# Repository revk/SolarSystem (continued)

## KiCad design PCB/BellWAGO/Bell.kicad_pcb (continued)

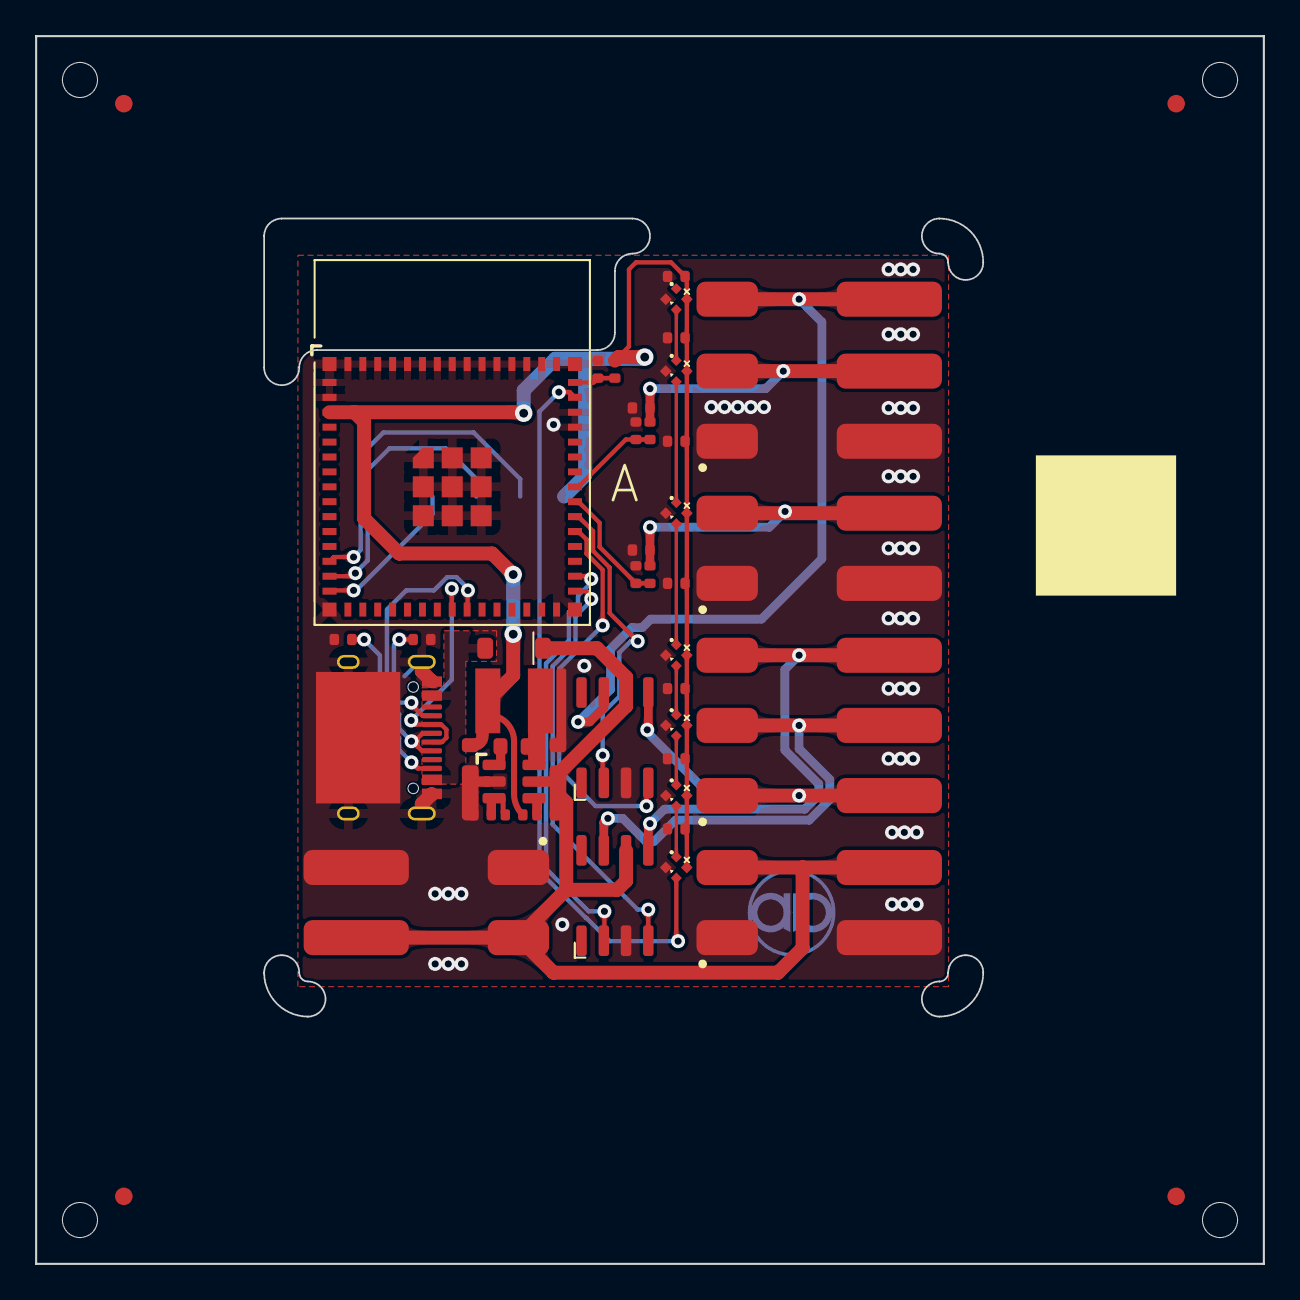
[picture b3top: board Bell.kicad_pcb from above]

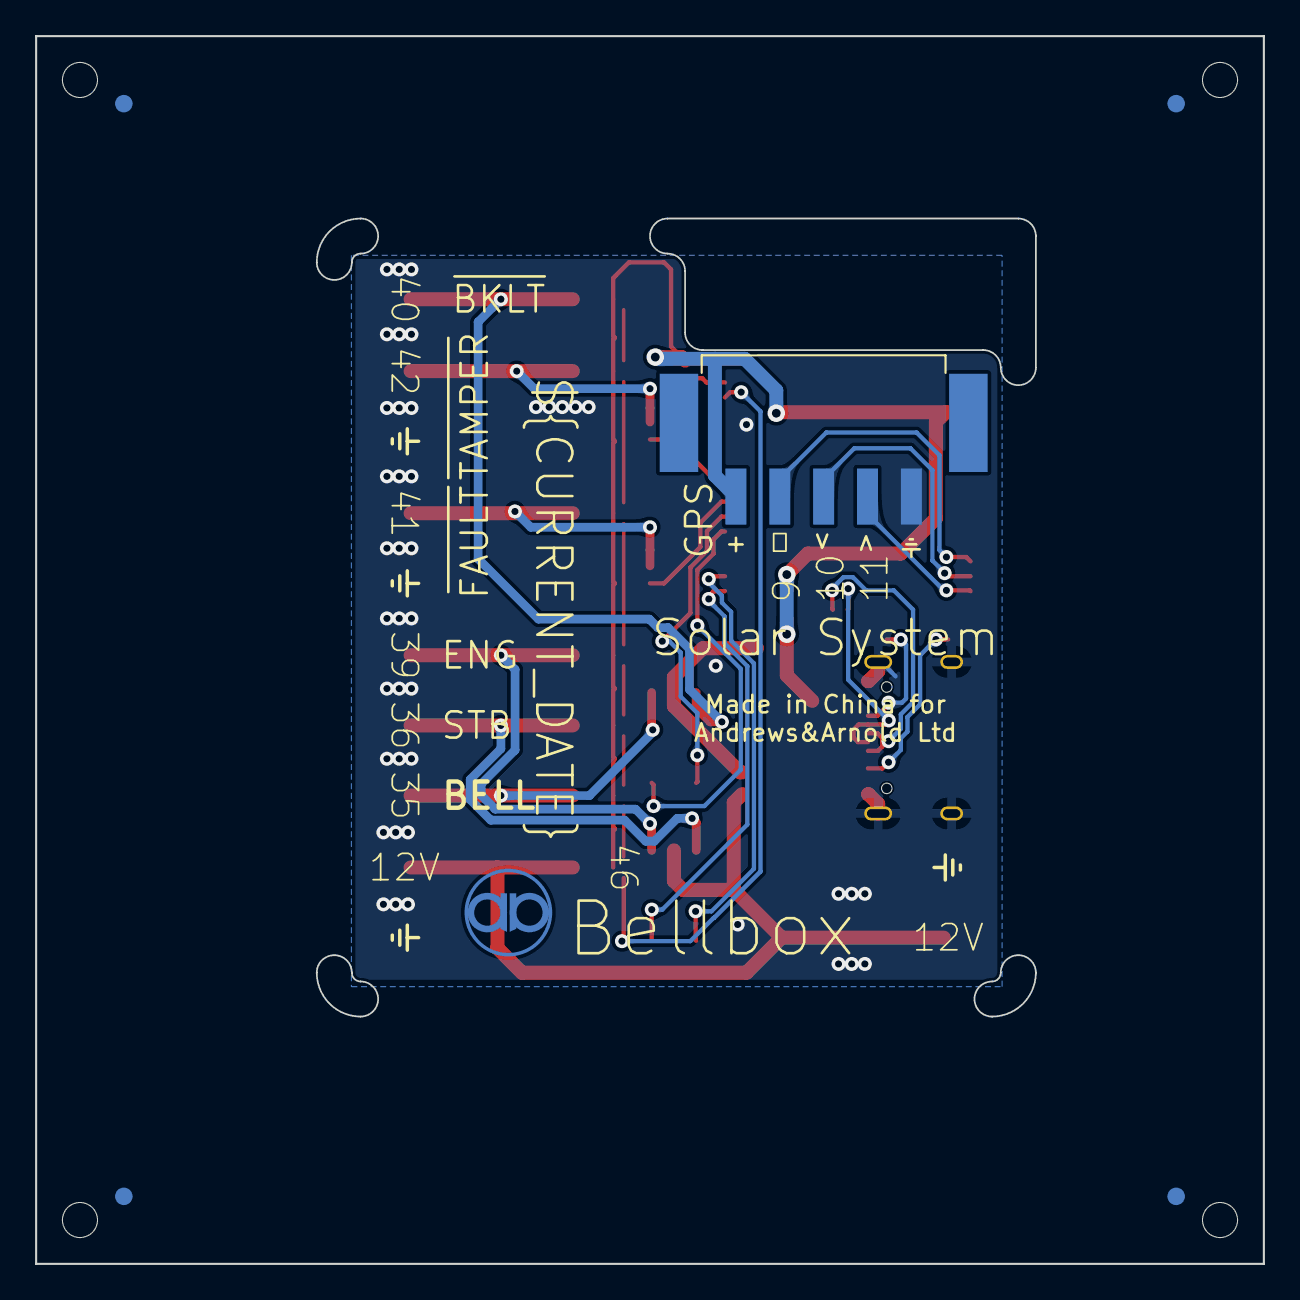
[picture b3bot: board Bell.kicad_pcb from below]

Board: 2 copper layers, 70.0 x 70.0 mm, 50 parts (3 on the bottom side), 31 nets.

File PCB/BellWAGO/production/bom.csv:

Designator,Footprint,Quantity,Value,LCSC Part #
C1,C_0603_,1,10uF 35V,C194427
"C10, C11, C12, C13, C4, C5, C6",C_0402,7,100nF,
"C2, C3",C_0402,2,33pF,
C7,C_0603_,1,10uF 6.3V,C1691
C8,C_0402,1,1uF,
C9,C_0603_,1,100nF,
"D1, D10",DFN1006-2L,2,~,C5137770
"D2, D4, D5, D6, D7, D8, D9",SMD1010,7,XL-1010RGBC-WS2812B,C5349953
D3,D_SOD-123,1,MBR0530,C5204746
J1,USB-C-Socket-H,1,USB-C-Socket-V,C709357
"J10, J11",WAGO-2060-452-998-404,2,FAULT,C2765055
J2,WAGO-2060-451-998-404,1,BL,C2765054
J7,WAGO-2060-453-998-404,1,BELL,C2765056
"J8, J9",WAGO-2060-452-998-404,2,PWR,C2765055
L2,L_4x4_,1,10uH,C167879
R1,R_0402_,1,124k,
R2,R_0402_,1,40k2,
R3,R_0402_,1,1M,
"R4, R7",R_0402,2,100R,
"R5, R6",R_0402,2,5K1,
R8,R_0402,1,10K,
U1,SOT-23-6-MD8942,1,MD8942,C2684786
"U3, U4",SO-8_3.9x4.9mm_P1.27mm,2,ISL89410,C635887
U6,ESP32-S3-MINI-1,1,ESP32-S3-MINI-1,C3013941

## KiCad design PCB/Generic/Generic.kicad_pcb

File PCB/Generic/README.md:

# Generic

These files are for use in [KiCad](https://www.kicad.org).

## Trademark

This is an open source project, but bear in mind you cannot sell boards bearing the Andrews & Arnold Ltd name, the A&A logo, the registered trademark AJK logo, or the GS1 allocated EANs assigned to Andrews & Arnold Ltd.

## Images

*Auto generated 2025-08-12T13:39:20*

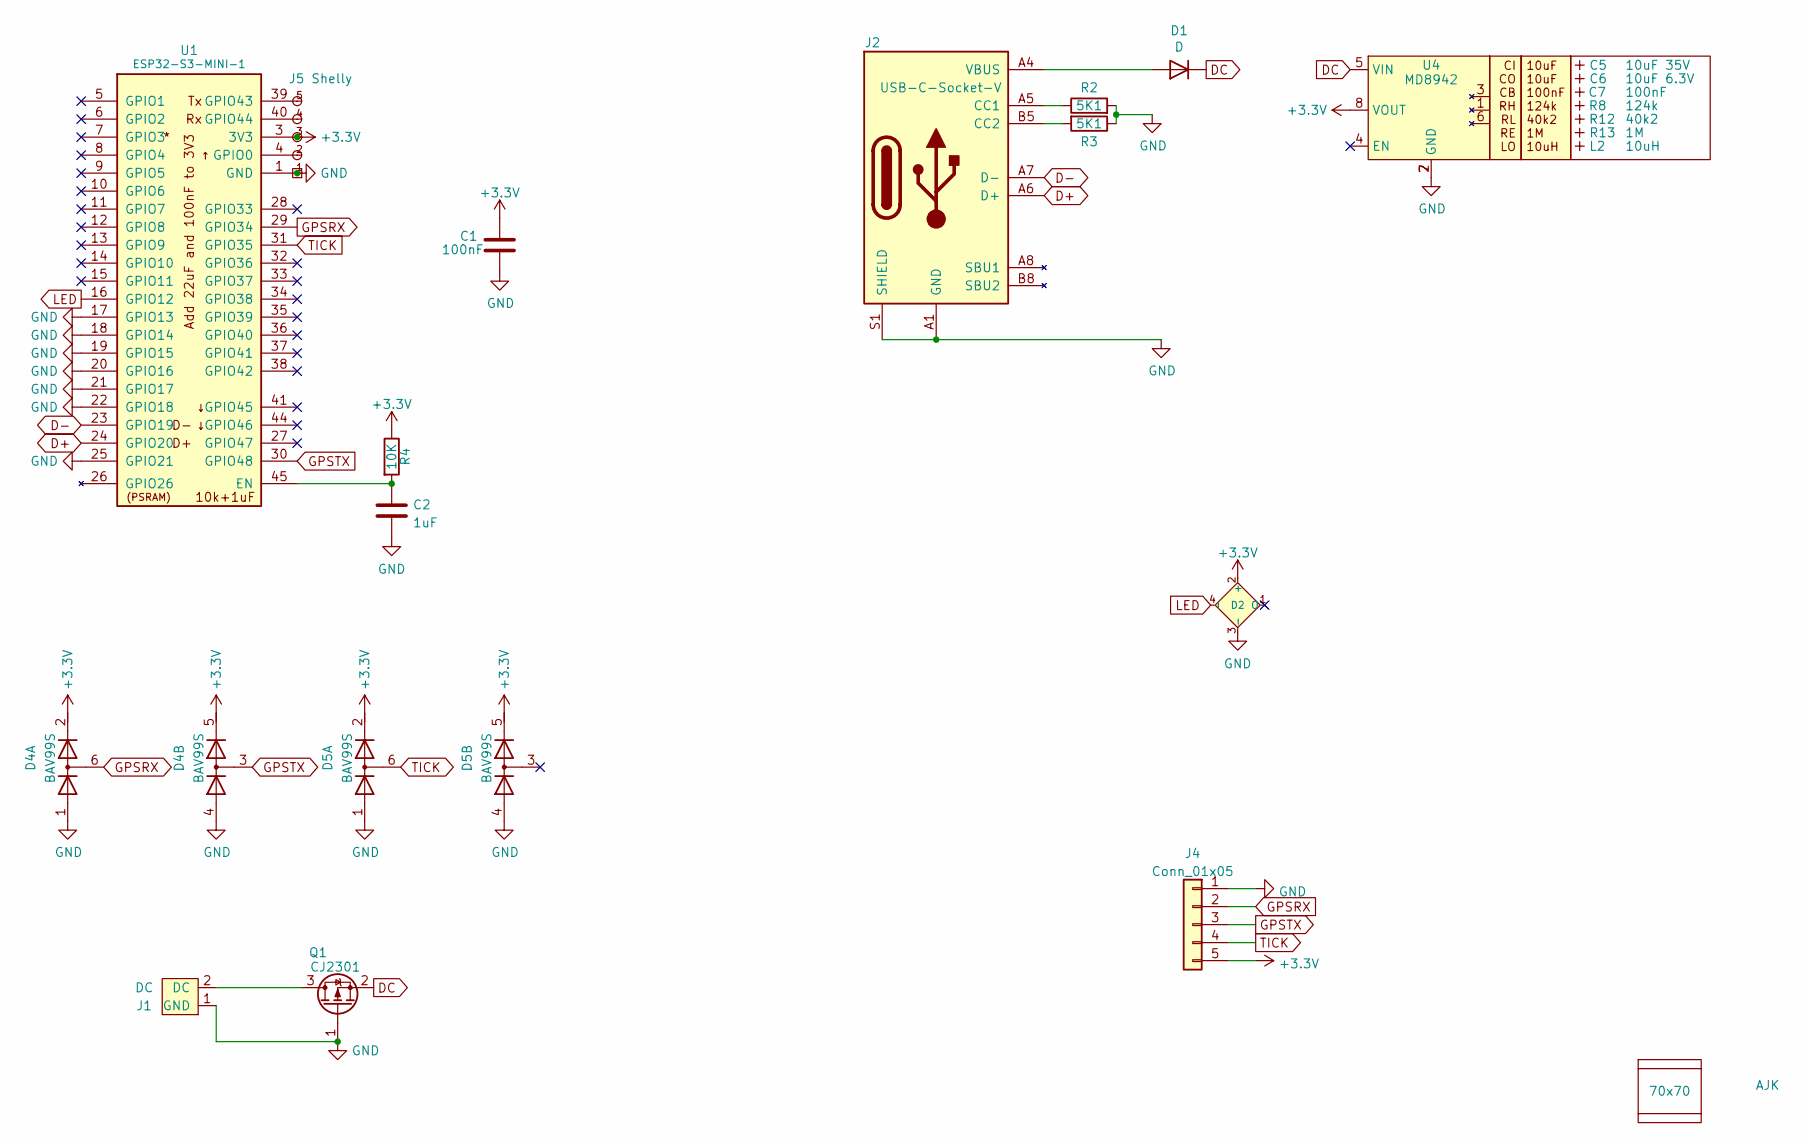
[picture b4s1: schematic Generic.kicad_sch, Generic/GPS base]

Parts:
C1: 100nF; C_0402
C2: 1uF; C_0402
C5: 10uF 35V; C_0603_; MPN C194427
C6: 10uF 6.3V; C_0603_; MPN C1691
C7: 100nF; C_0603_
D1: D; D_1206; MPN C143805
D2: XL-1010RGBC-WS2812B; SMD1010; MPN C5349953
D4, D5: BAV99S; SOT-363_SC-70-6
J1: DC; PTSM-HH-2-RA
J2: USB-C-Socket-V; USB-C-Socket-H; MPN C709357
J4: Conn_01x05; PTSM-HH-5-RA
J5: Shelly
L2: 10uH; L_4x4_
Logo2: AJK
PCB1: 70x70; PCB7070
Q1: CJ2301; SOT-23; MPN C2910170
R2, R3: 5K1; R_0402
R4: 10K; R_0402
R8: 124k; R_0402_
R12: 40k2; R_0402_
R13: 1M; R_0402_
U1: ESP32-S3-MINI-1; MPN C3013941
U4: MD8942; SOT-23-6-MD8942; MPN C2684786
V1, V2: VCUT70

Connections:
+3.3V: C1.1, D2.2 (+), D4.2 (K2), D4.5 (K4), D5.2 (K2), D5.5 (K4), J4.5, J5.3 (3V3), R4.1, U1.3 (3V3), U4.8 (VOUT)
D+: J2.A6 (D+), J2.B6 (D+), U1.24 (GPIO20)
D-: J2.A7 (D-), J2.B7 (D-), U1.23 (GPIO19)
DC: D1.1 (K), Q1.2 (S), U4.5 (VIN)
GND: C1.2, C2.2, D2.3 (-), D4.1 (A1), D4.4 (A3), D5.1 (A1), D5.4 (A3), J1.1 (GND), J2.A1 (GND), J2.A12 (GND), J2.B1 (GND), J2.B12 (GND), J2.S1 (SHIELD), J4.1, J5.1 (GND), Q1.1 (G), R2.2, R3.1, U1.1 (GND), U1.2 (GND), U1.17 (GPIO13), U1.18 (GPIO14), U1.19 (GPIO15), U1.20 (GPIO16), U1.21 (GPIO17), U1.22 (GPIO18), U1.25 (GPIO21), U1.42 (GND), U1.43 (GND), U1.46 (GND), U1.47 (GND), U1.48 (GND), U1.49 (GND), U1.50 (GND), U1.51 (GND), U1.52 (GND), U1.53 (GND), U1.54 (GND), U1.55 (GND), U1.56 (GND), U1.57 (GND), U1.58 (GND), U1.59 (GND), U1.60 (GND), U1.61 (GND), U1.62 (GND), U1.63 (GND), U1.64 (GND), U1.65 (GND), U4.2 (GND), U4.7 (GND)
GPSRX: D4.6 (K3A4), J4.2, U1.29 (GPIO34)
GPSTX: D4.3 (K1A2), J4.3, U1.30 (GPIO48)
LED: D2.4 (I), U1.16 (GPIO12)
unnamed: D1.2 (A), J2.A4 (VBUS), J2.A9 (VBUS), J2.B4 (VBUS), J2.B9 (VBUS)
unnamed: J1.2 (DC), Q1.3 (D)
unnamed: J2.A5 (CC1), R2.1
unnamed: J2.B5 (CC2), R3.2
unnamed: J5.2 (0), U1.4 (GPIO0)
unnamed: J5.4 (Rx), U1.40 (GPIO44)
unnamed: J5.5 (Tx), U1.39 (GPIO43)
unnamed: C2.1, R4.2, U1.45 (EN)
TICK: D5.6 (K3A4), J4.4, U1.31 (GPIO35)

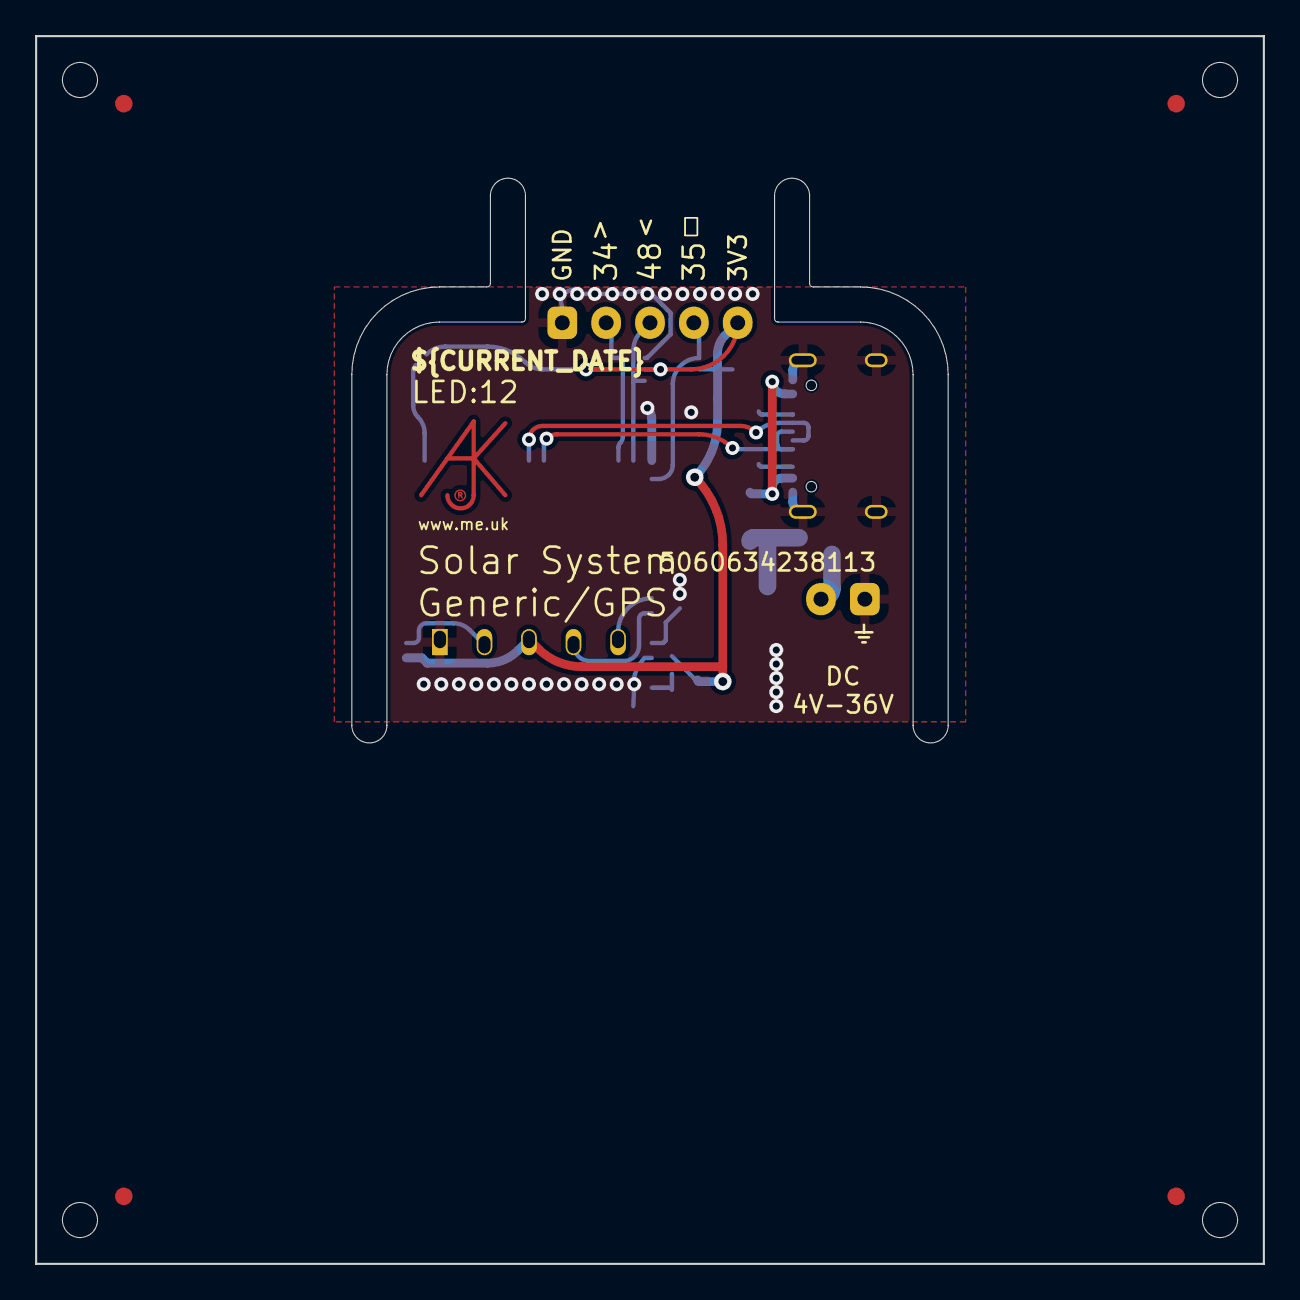
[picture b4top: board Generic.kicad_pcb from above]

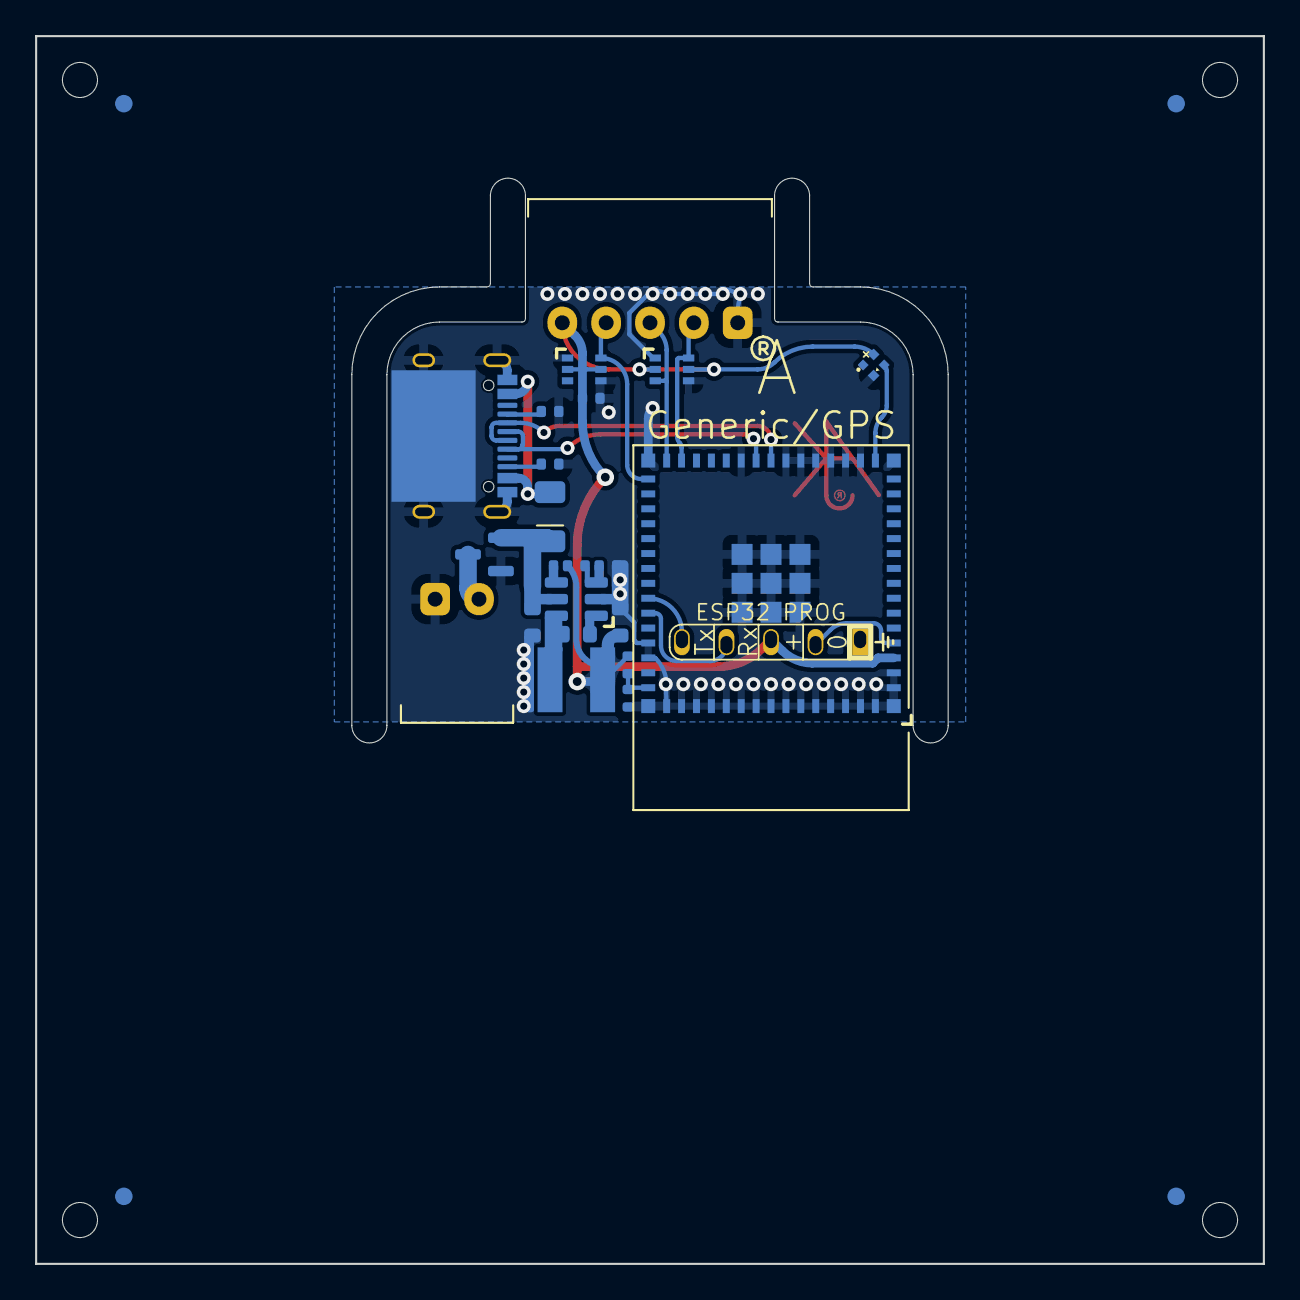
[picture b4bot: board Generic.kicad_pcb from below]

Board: 2 copper layers, 70.0 x 70.0 mm, 27 parts (25 on the bottom side), 17 nets.

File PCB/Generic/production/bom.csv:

Designator,Footprint,Quantity,Value,LCSC Part #
C1,C_0402,1,100nF,
C2,C_0402,1,1uF,
C5,C_0603_,1,10uF 35V,C194427
C6,C_0603_,1,10uF 6.3V,C1691
C7,C_0603_,1,100nF,
D1,D_1206,1,D,C143805
D2,SMD1010,1,XL-1010RGBC-WS2812B,C5349953
"D4, D5",SOT-363_SC-70-6,2,BAV99S,
J1,PTSM-HH-2-RA,1,DC,
J2,USC16-TR,1,USB-C,C709357
J4,PTSM-HH-5-RA,1,Conn_01x05,
L2,L_4x4_,1,10uH,
Q1,SOT-23,1,CJ2301,
R12,R_0402_,1,40k2,
R13,R_0402_,1,1M,
"R2, R3",R_0402,2,5K1,
R4,R_0402,1,10K,
R8,R_0402_,1,124k,
U1,ESP32-S3-MINI-1,1,ESP32-S3-MINI-1,C3013941
U4,SOT-23-6-MD8942,1,MD8942,C2684786

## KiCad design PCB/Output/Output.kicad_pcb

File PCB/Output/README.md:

# Output

These files are for use in [KiCad](https://www.kicad.org).

## Trademark

This is an open source project, but bear in mind you cannot sell boards bearing the Andrews & Arnold Ltd name, the A&A logo, the registered trademark AJK logo, or the GS1 allocated EANs assigned to Andrews & Arnold Ltd.

## Images

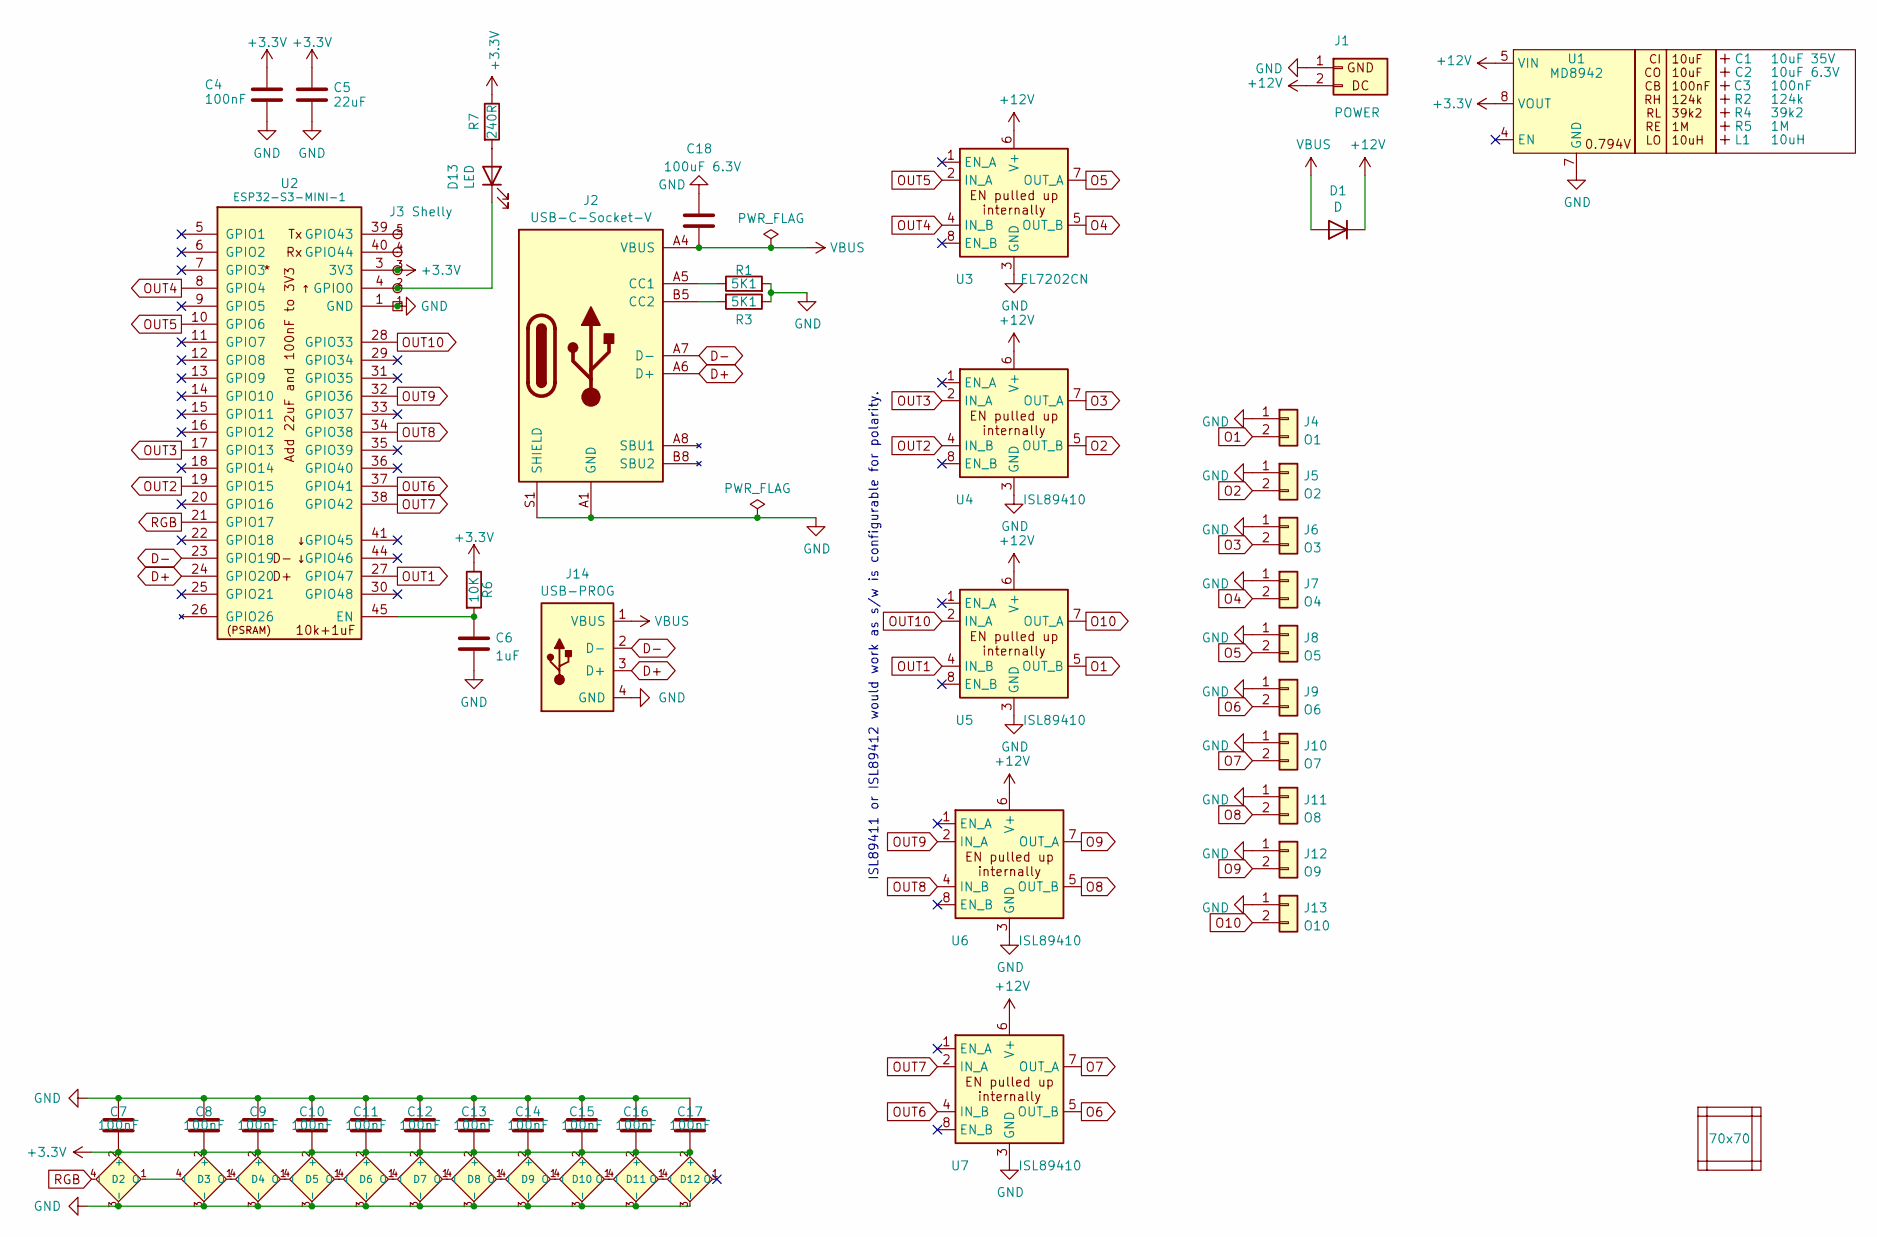
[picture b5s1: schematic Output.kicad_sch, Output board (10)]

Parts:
C1: 10uF 35V; C_0603_; MPN C194427
C2: 10uF 6.3V; C_0603_; MPN C1691
C3: 100nF; C_0603_
C4, C7, C8, C9, C10, C11, C12, C13, C14, C15, C16, C17: 100nF; C_0402
C5: 22uF; C_0402
C6: 1uF; C_0402
C18: 100uF 6.3V; C_1206
D1: D; D_SOD-123; MPN C1884542
D2, D3, D4, D5, D6, D7, D8, D9, D10, D11, D12: XL-1010RGBC-WS2812B; SMD1010; MPN C5349953
D13: LED; LED_0402_1005Metric; MPN C965790
J1: POWER; PTSM-HH1-2-RA
J2: USB-C-Socket-V; USB-C-Socket-H; MPN C709357
J3: Shelly
J4: O1; PTSM-HH1-2-RA
J5: O2; PTSM-HH1-2-RA
J6: O3; PTSM-HH1-2-RA
J7: O4; PTSM-HH1-2-RA
J8: O5; PTSM-HH1-2-RA
J9: O6; PTSM-HH1-2-RA
J10: O7; PTSM-HH1-2-RA
J11: O8; PTSM-HH1-2-RA
J12: O9; PTSM-HH1-2-RA
J13: O10; PTSM-HH1-2-RA
J14: USB-PROG
L1: 10uH; L_4x4_
PCB1: 70x70; PCB7070
R1, R3: 5K1; R_0402
R2: 124k; R_0402_
R4: 39k2; R_0402_
R5: 1M; R_0402_
R6: 10K; R_0402
R7: 240R; R_0402
U1: MD8942; SOT-23-6-MD8942; MPN C2684786
U2: ESP32-S3-MINI-1; MPN C3013941
U3: EL7202CN; SO-8_3.9x4.9mm_P1.27mm; MPN C2924635
U4, U5, U6, U7: ISL89410; SO-8_3.9x4.9mm_P1.27mm; MPN C2924635
V1, V2, V3, V4: VCUT70N

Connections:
+3.3V: C4.1, C5.1, C7.2, C8.2, C9.2, C10.2, C11.2, C12.2, C13.2, C14.2, C15.2, C16.2, C17.2, D2.2 (+), D3.2 (+), D4.2 (+), D5.2 (+), D6.2 (+), D7.2 (+), D8.2 (+), D9.2 (+), D10.2 (+), D11.2 (+), D12.2 (+), J3.3 (3V3), R6.1, R7.1, U1.8 (VOUT), U2.3 (3V3)
+12V: D1.1 (K), J1.2 (DC), U1.5 (VIN), U3.6 (V+), U4.6 (V+), U5.6 (V+), U6.6 (V+), U7.6 (V+)
D+: J2.A6 (D+), J2.B6 (D+), J14.3 (D+), U2.24 (GPIO20)
D-: J2.A7 (D-), J2.B7 (D-), J14.2 (D-), U2.23 (GPIO19)
GND: C4.2, C5.2, C6.2, C7.1, C8.1, C9.1, C10.1, C11.1, C12.1, C13.1, C14.1, C15.1, C16.1, C17.1, C18.1, D2.3 (-), D3.3 (-), D4.3 (-), D5.3 (-), D6.3 (-), D7.3 (-), D8.3 (-), D9.3 (-), D10.3 (-), D11.3 (-), D12.3 (-), J1.1 (GND), J2.A1 (GND), J2.A12 (GND), J2.B1 (GND), J2.B12 (GND), J2.S1 (SHIELD), J3.1 (GND), J4.1, J5.1, J6.1, J7.1, J8.1, J9.1, J10.1, J11.1, J12.1, J13.1, J14.4 (GND), R1.2, R3.1, U1.2 (GND), U1.7 (GND), U2.1 (GND), U2.2 (GND), U2.42 (GND), U2.43 (GND), U2.46 (GND), U2.47 (GND), U2.48 (GND), U2.49 (GND), U2.50 (GND), U2.51 (GND), U2.52 (GND), U2.53 (GND), U2.54 (GND), U2.55 (GND), U2.56 (GND), U2.57 (GND), U2.58 (GND), U2.59 (GND), U2.60 (GND), U2.61 (GND), U2.62 (GND), U2.63 (GND), U2.64 (GND), U2.65 (GND), U3.3 (GND), U4.3 (GND), U5.3 (GND), U6.3 (GND), U7.3 (GND)
unnamed: D2.1 (O), D3.4 (I)
unnamed: D3.1 (O), D4.4 (I)
unnamed: D4.1 (O), D5.4 (I)
unnamed: D5.1 (O), D6.4 (I)
unnamed: D6.1 (O), D7.4 (I)
unnamed: D7.1 (O), D8.4 (I)
unnamed: D8.1 (O), D9.4 (I)
unnamed: D9.1 (O), D10.4 (I)
unnamed: D10.1 (O), D11.4 (I)
unnamed: D11.1 (O), D12.4 (I)
unnamed: D13.2 (A), R7.2
unnamed: D13.1 (K), J3.2 (0), U2.4 (GPIO0)
unnamed: J2.A5 (CC1), R1.1
unnamed: J2.B5 (CC2), R3.2
unnamed: J3.4 (Rx), U2.40 (GPIO44)
unnamed: J3.5 (Tx), U2.39 (GPIO43)
unnamed: C6.1, R6.2, U2.45 (EN)
O1: J4.2, U5.5 (OUT_B)
O2: J5.2, U4.5 (OUT_B)
O3: J6.2, U4.7 (OUT_A)
O4: J7.2, U3.5 (OUT_B)
O5: J8.2, U3.7 (OUT_A)
O6: J9.2, U7.5 (OUT_B)
O7: J10.2, U7.7 (OUT_A)
O8: J11.2, U6.5 (OUT_B)
O9: J12.2, U6.7 (OUT_A)
O10: J13.2, U5.7 (OUT_A)
OUT1: U2.27 (GPIO47), U5.4 (IN_B)
OUT2: U2.19 (GPIO15), U4.4 (IN_B)
OUT3: U2.17 (GPIO13), U4.2 (IN_A)
OUT4: U2.8 (GPIO4), U3.4 (IN_B)
OUT5: U2.10 (GPIO6), U3.2 (IN_A)
OUT6: U2.37 (GPIO41), U7.4 (IN_B)
OUT7: U2.38 (GPIO42), U7.2 (IN_A)
OUT8: U2.34 (GPIO38), U6.4 (IN_B)
OUT9: U2.32 (GPIO36), U6.2 (IN_A)
OUT10: U2.28 (GPIO33), U5.2 (IN_A)
RGB: D2.4 (I), U2.21 (GPIO17)
VBUS: C18.2, D1.2 (A), J2.A4 (VBUS), J2.A9 (VBUS), J2.B4 (VBUS), J2.B9 (VBUS), J14.1 (VBUS)

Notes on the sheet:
ISL89411 or ISL89412 would work as s/w is configurable for polarity.

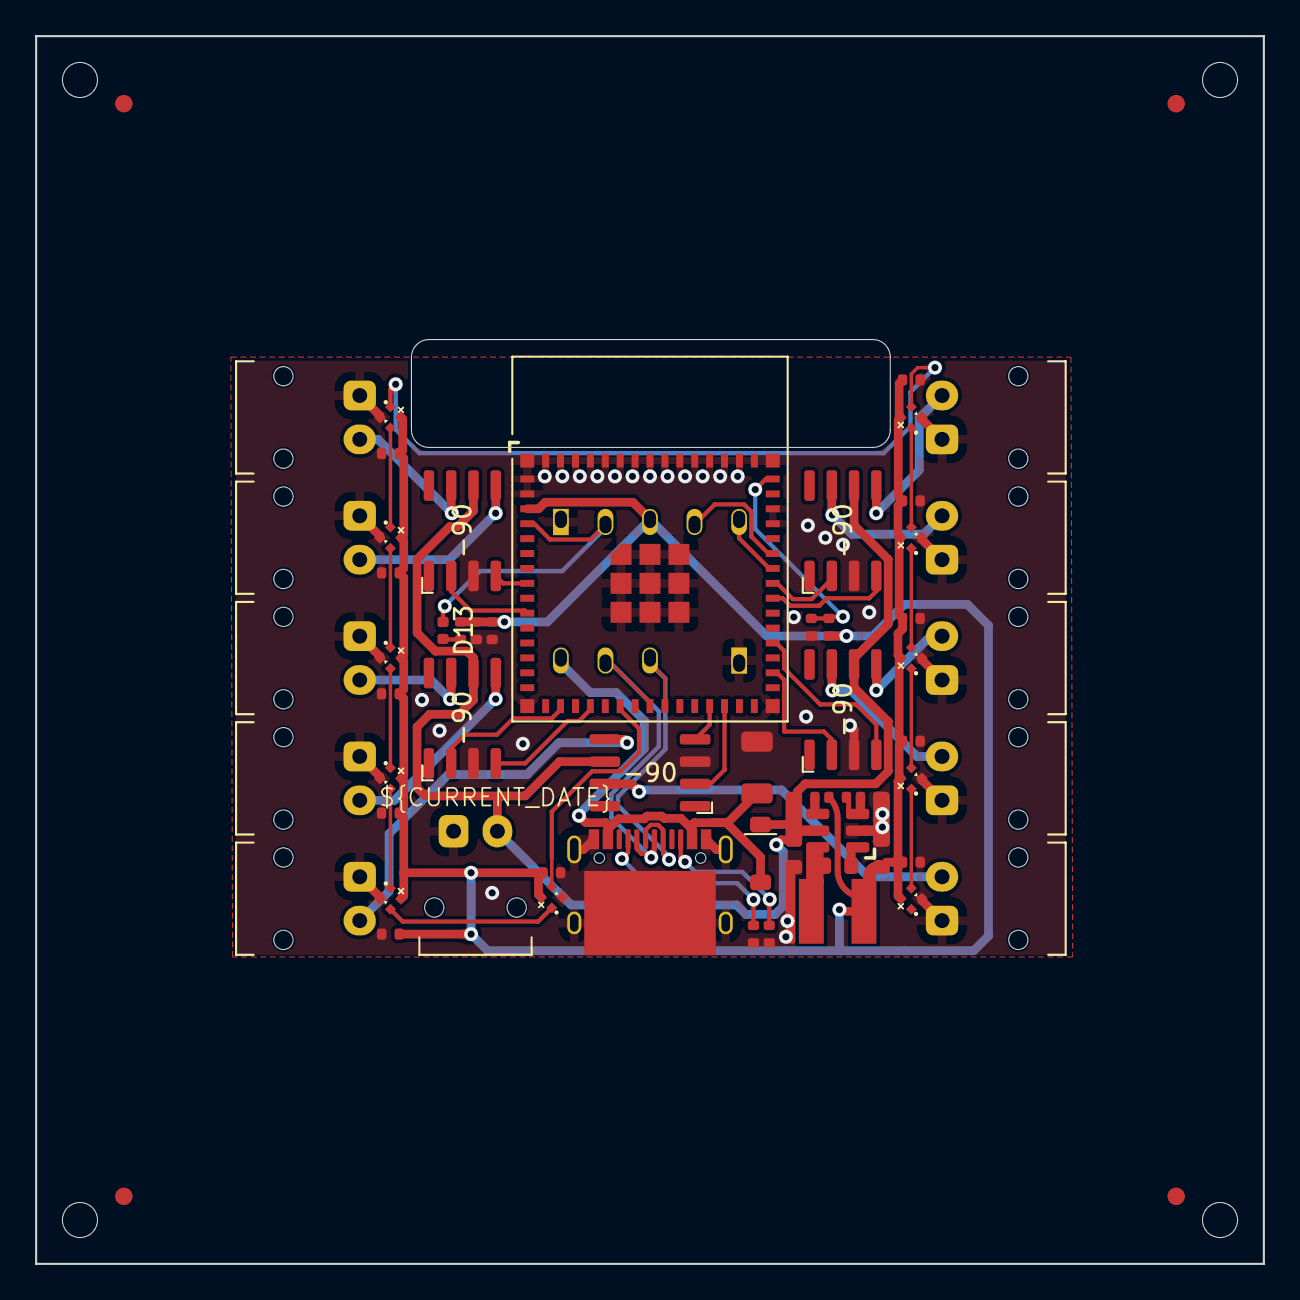
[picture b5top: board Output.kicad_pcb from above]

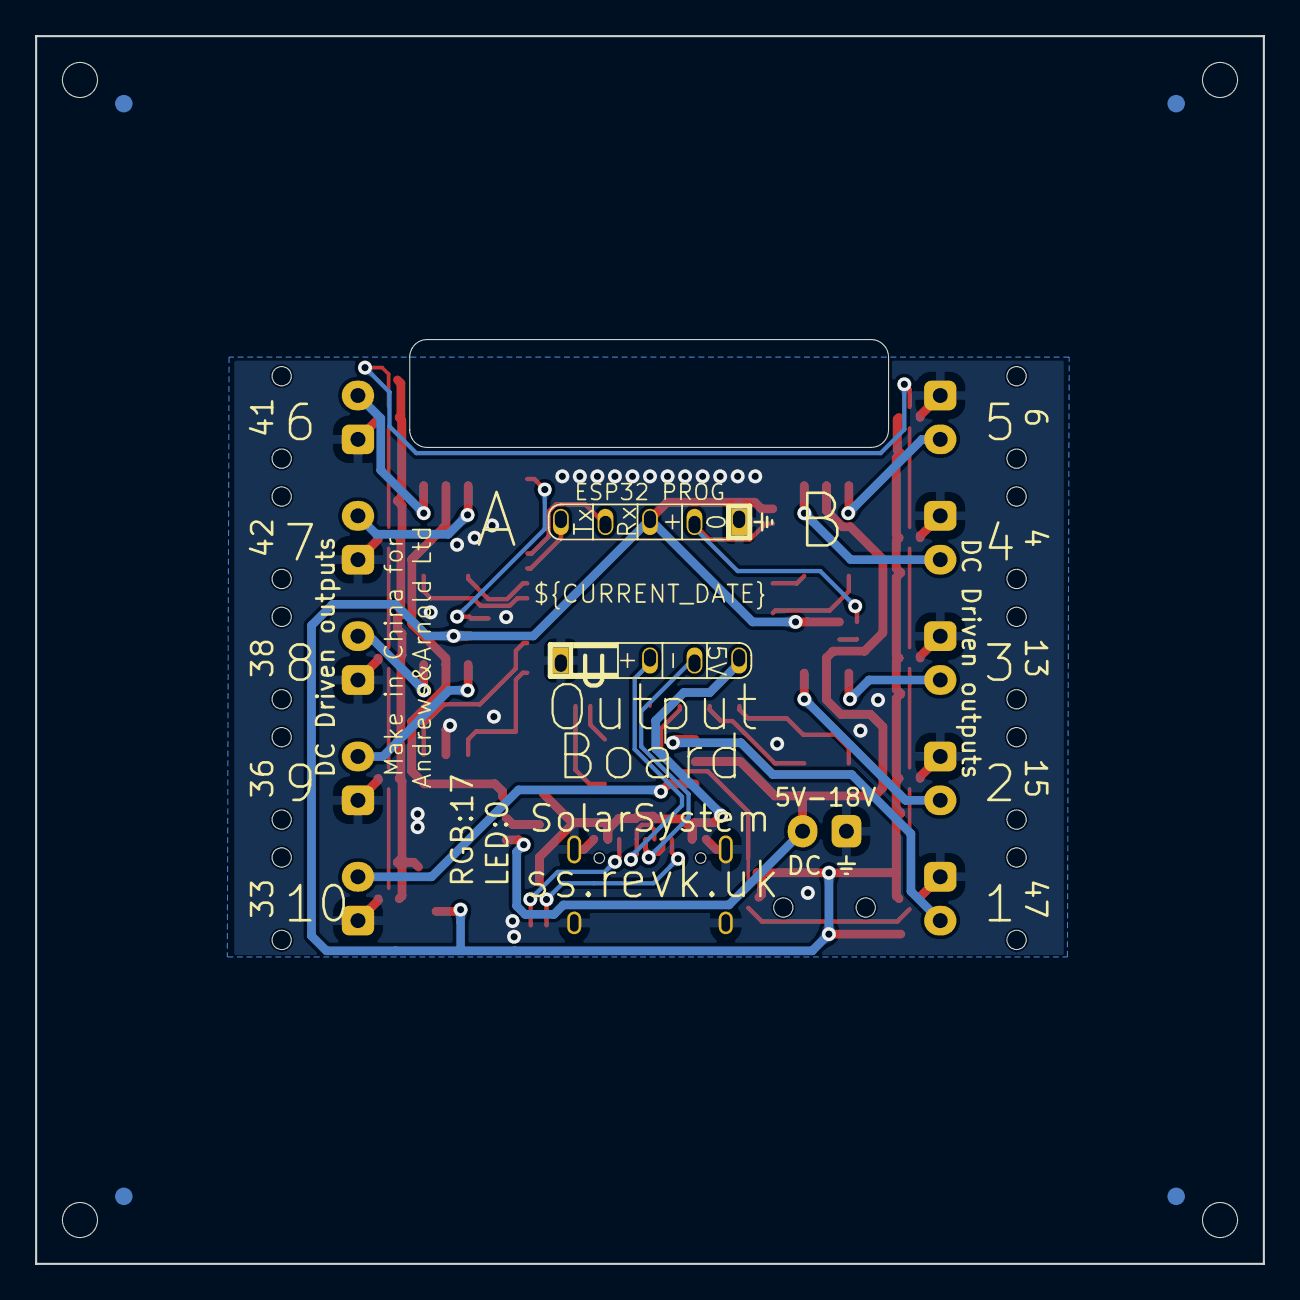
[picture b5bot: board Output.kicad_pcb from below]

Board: 2 copper layers, 70.0 x 70.0 mm, 65 parts (2 on the bottom side), 44 nets.

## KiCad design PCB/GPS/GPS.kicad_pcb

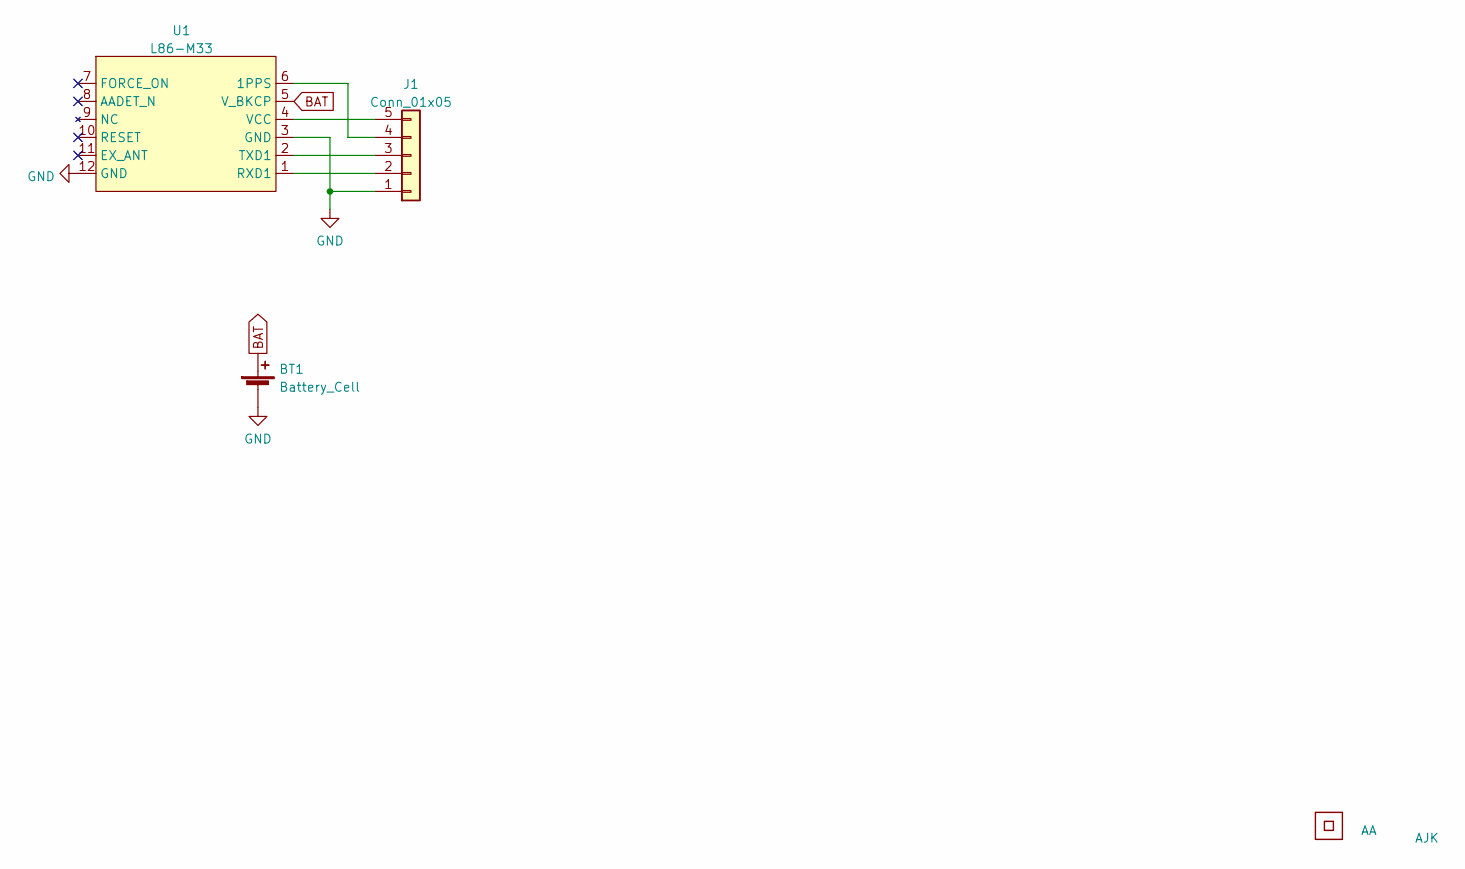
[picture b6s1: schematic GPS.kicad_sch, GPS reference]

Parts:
BT1: Battery_Cell; Battery-Holder-2032
J1: Conn_01x05; PTSM-HH-5-RA-P-SMD
Logo1: AA
Logo2: AJK
U1: L86-M33
U5: QR; QR-SS

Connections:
BAT: BT1.1 (+), U1.5 (V_BKCP)
GND: BT1.2 (-), J1.1, U1.3 (GND), U1.12 (GND)
unnamed: J1.2, U1.1 (RXD1)
unnamed: J1.3, U1.2 (TXD1)
unnamed: J1.4, U1.6 (1PPS)
unnamed: J1.5, U1.4 (VCC)

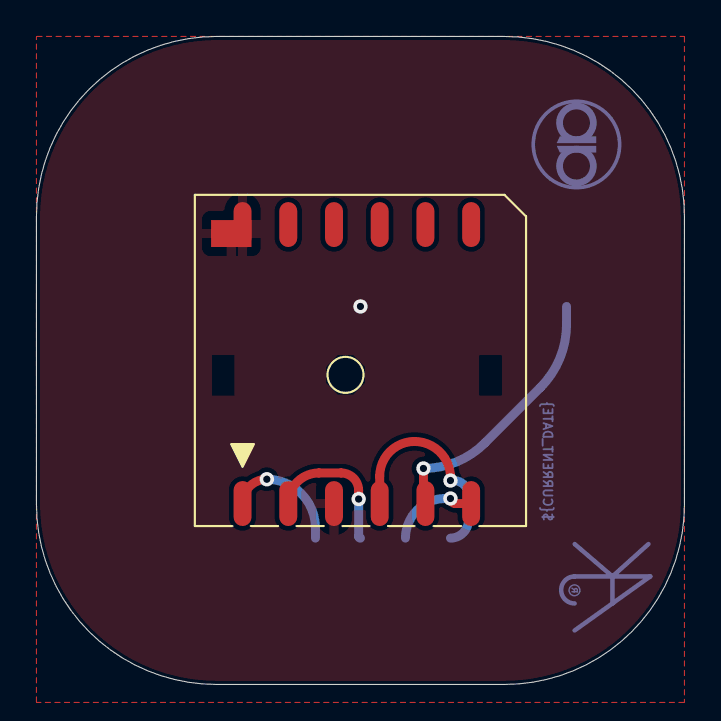
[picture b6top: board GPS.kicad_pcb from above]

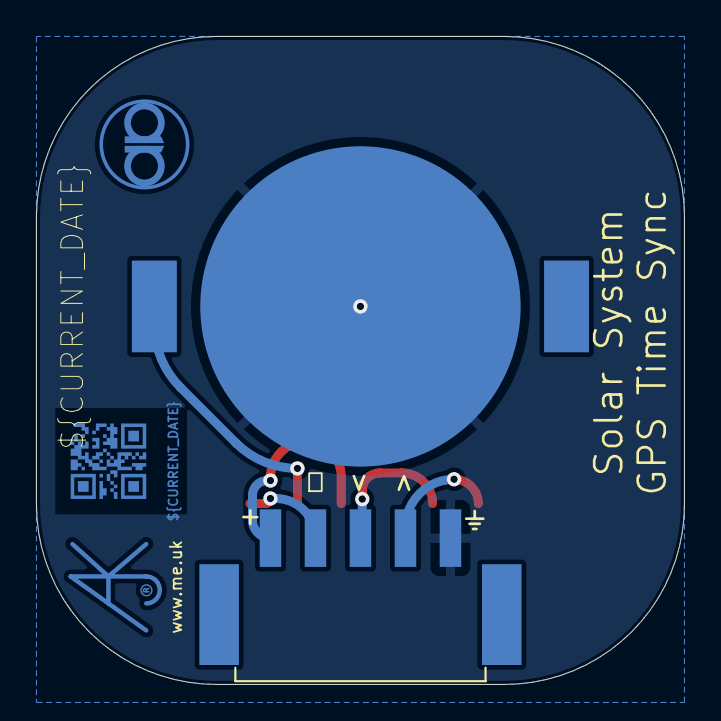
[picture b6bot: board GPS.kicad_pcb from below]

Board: 2 copper layers, 36.0 x 36.0 mm, 6 parts (5 on the bottom side), 6 nets.
